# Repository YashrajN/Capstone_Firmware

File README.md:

# Capstone_Firmware
Firmware for autonomous shingle installation robot

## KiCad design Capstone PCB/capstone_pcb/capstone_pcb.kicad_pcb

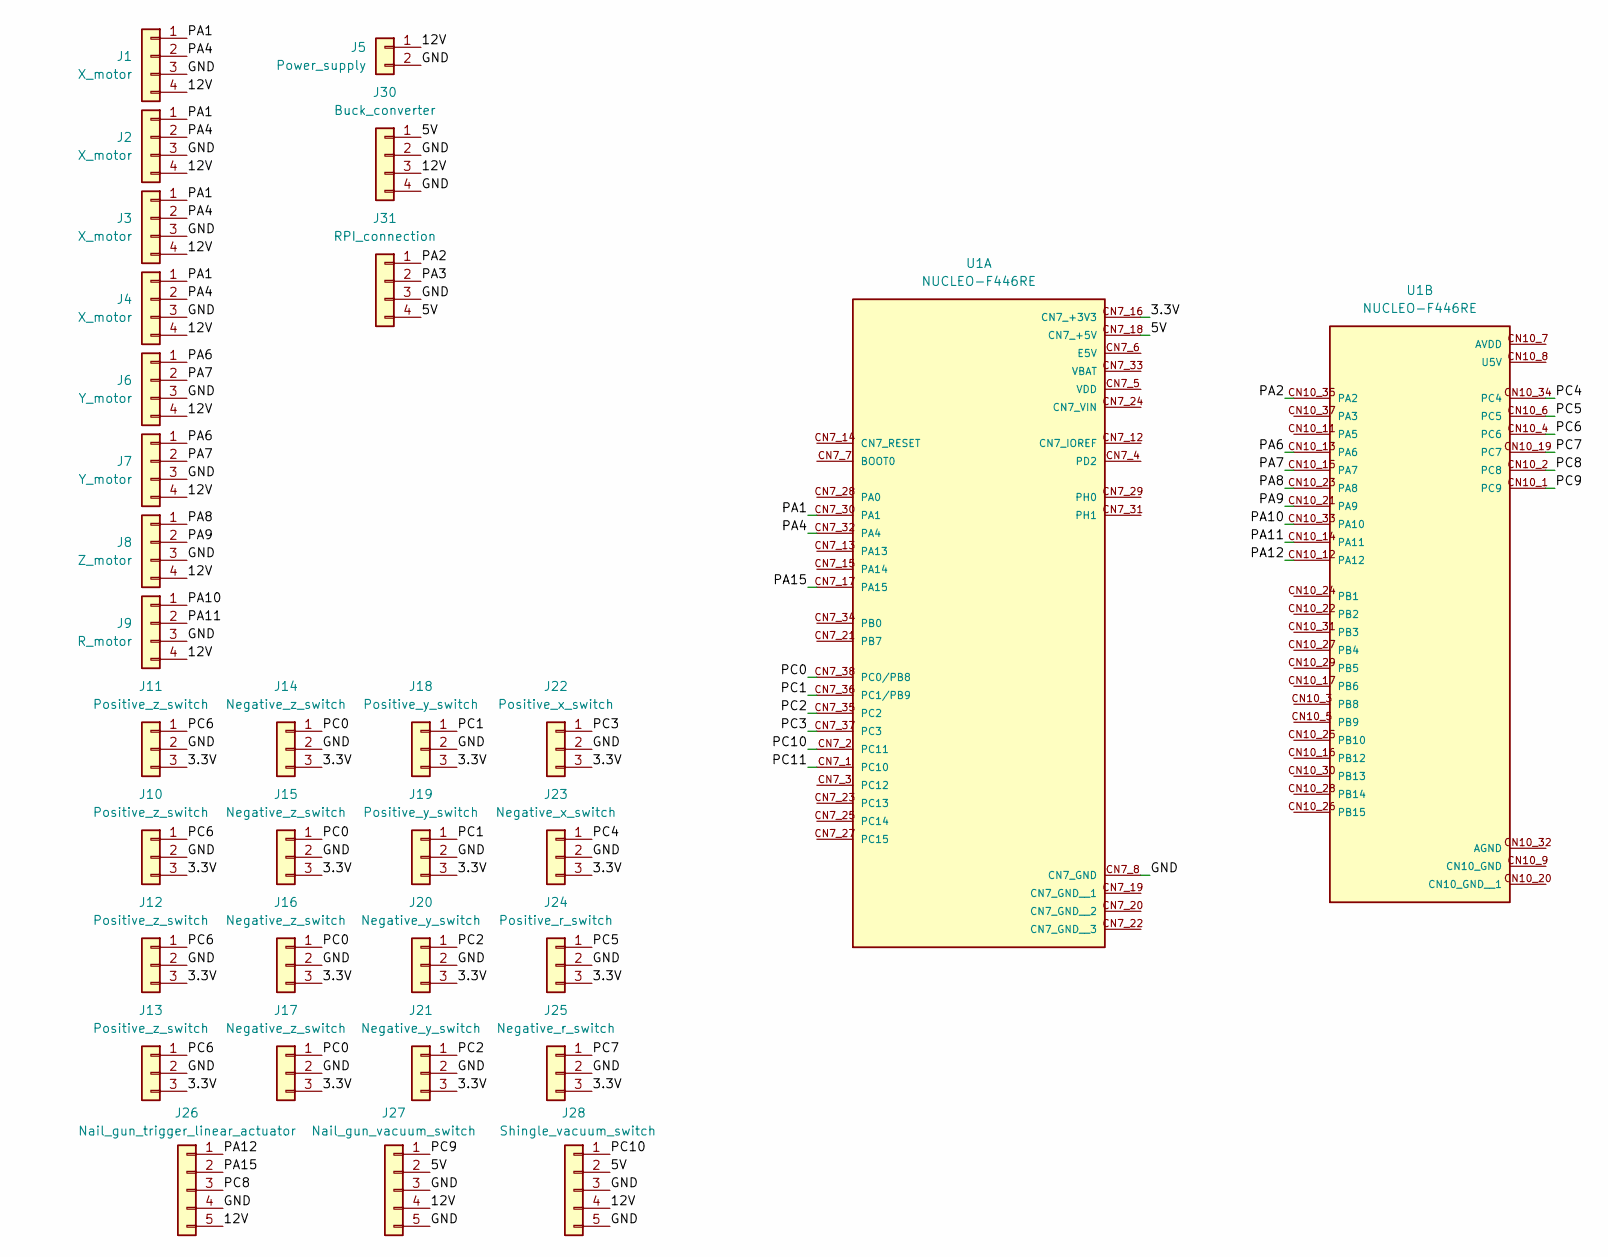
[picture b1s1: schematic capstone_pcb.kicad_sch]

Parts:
J1, J2, J3, J4: X_motor; JST_XH_B4B-XH-A_1x04_P2.50mm_Vertical
J5: Power_supply; JST_VH_B2P-VH_1x02_P3.96mm_Vertical
J6, J7: Y_motor; JST_XH_B4B-XH-A_1x04_P2.50mm_Vertical
J8: Z_motor; JST_XH_B4B-XH-A_1x04_P2.50mm_Vertical
J9: R_motor; JST_XH_B4B-XH-A_1x04_P2.50mm_Vertical
J10, J11, J12, J13: Positive_z_switch; JST_XH_B3B-XH-A_1x03_P2.50mm_Vertical
J14, J15, J16, J17: Negative_z_switch; JST_XH_B3B-XH-A_1x03_P2.50mm_Vertical
J18, J19: Positive_y_switch; JST_XH_B3B-XH-A_1x03_P2.50mm_Vertical
J20, J21: Negative_y_switch; JST_XH_B3B-XH-A_1x03_P2.50mm_Vertical
J22: Positive_x_switch; JST_XH_B3B-XH-A_1x03_P2.50mm_Vertical
J23: Negative_x_switch; JST_XH_B3B-XH-A_1x03_P2.50mm_Vertical
J24: Positive_r_switch; JST_XH_B3B-XH-A_1x03_P2.50mm_Vertical
J25: Negative_r_switch; JST_XH_B3B-XH-A_1x03_P2.50mm_Vertical
J26: Nail_gun_trigger_linear_actuator; JST_XH_B5B-XH-A_1x05_P2.50mm_Vertical
J27: Nail_gun_vacuum_switch; JST_XH_B5B-XH-A_1x05_P2.50mm_Vertical
J28: Shingle_vacuum_switch; JST_XH_B5B-XH-A_1x05_P2.50mm_Vertical
J30: Buck_converter; JST_XH_B4B-XH-A_1x04_P2.50mm_Vertical
J31: RPI_connection; JST_XH_B4B-XH-A_1x04_P2.50mm_Vertical
U1: NUCLEO-F446RE; MODULE_NUCLEO-F446RE; PARTREV 13

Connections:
/3.3V: J10.3, J11.3, J12.3, J13.3, J14.3, J15.3, J16.3, J17.3, J18.3, J19.3, J20.3, J21.3, J22.3, J23.3, J24.3, J25.3, U1.CN7_16 (CN7_+3V3)
/5V: J27.2, J28.2, J30.1, J31.4, U1.CN7_18 (CN7_+5V)
/12V: J1.4, J2.4, J3.4, J4.4, J5.1, J6.4, J7.4, J8.4, J9.4, J26.5, J27.4, J28.4, J30.3
/GND: J1.3, J2.3, J3.3, J4.3, J5.2, J6.3, J7.3, J8.3, J9.3, J10.2, J11.2, J12.2, J13.2, J14.2, J15.2, J16.2, J17.2, J18.2, J19.2, J20.2, J21.2, J22.2, J23.2, J24.2, J25.2, J26.4, J27.3, J27.5, J28.3, J28.5, J30.2, J30.4, J31.3, U1.CN7_8 (CN7_GND)
/PA1: J1.1, J2.1, J3.1, J4.1, U1.CN7_30 (PA1)
/PA2: J31.1, U1.CN10_35 (PA2)
/PA3: J31.2
/PA4: J1.2, J2.2, J3.2, J4.2, U1.CN7_32 (PA4)
/PA6: J6.1, J7.1, U1.CN10_13 (PA6)
/PA7: J6.2, J7.2, U1.CN10_15 (PA7)
/PA8: J8.1, U1.CN10_23 (PA8)
/PA9: J8.2, U1.CN10_21 (PA9)
/PA10: J9.1, U1.CN10_33 (PA10)
/PA11: J9.2, U1.CN10_14 (PA11)
/PA12: J26.1, U1.CN10_12 (PA12)
/PA15: J26.2, U1.CN7_17 (PA15)
/PC0: J14.1, J15.1, J16.1, J17.1, U1.CN7_38 (PC0/PB8)
/PC1: J18.1, J19.1, U1.CN7_36 (PC1/PB9)
/PC2: J20.1, J21.1, U1.CN7_35 (PC2)
/PC3: J22.1, U1.CN7_37 (PC3)
/PC4: J23.1, U1.CN10_34 (PC4)
/PC5: J24.1, U1.CN10_6 (PC5)
/PC6: J10.1, J11.1, J12.1, J13.1, U1.CN10_4 (PC6)
/PC7: J25.1, U1.CN10_19 (PC7)
/PC8: J26.3, U1.CN10_2 (PC8)
/PC9: J27.1, U1.CN10_1 (PC9)
/PC10: J28.1, U1.CN7_2 (PC11)
/PC11: U1.CN7_1 (PC10)

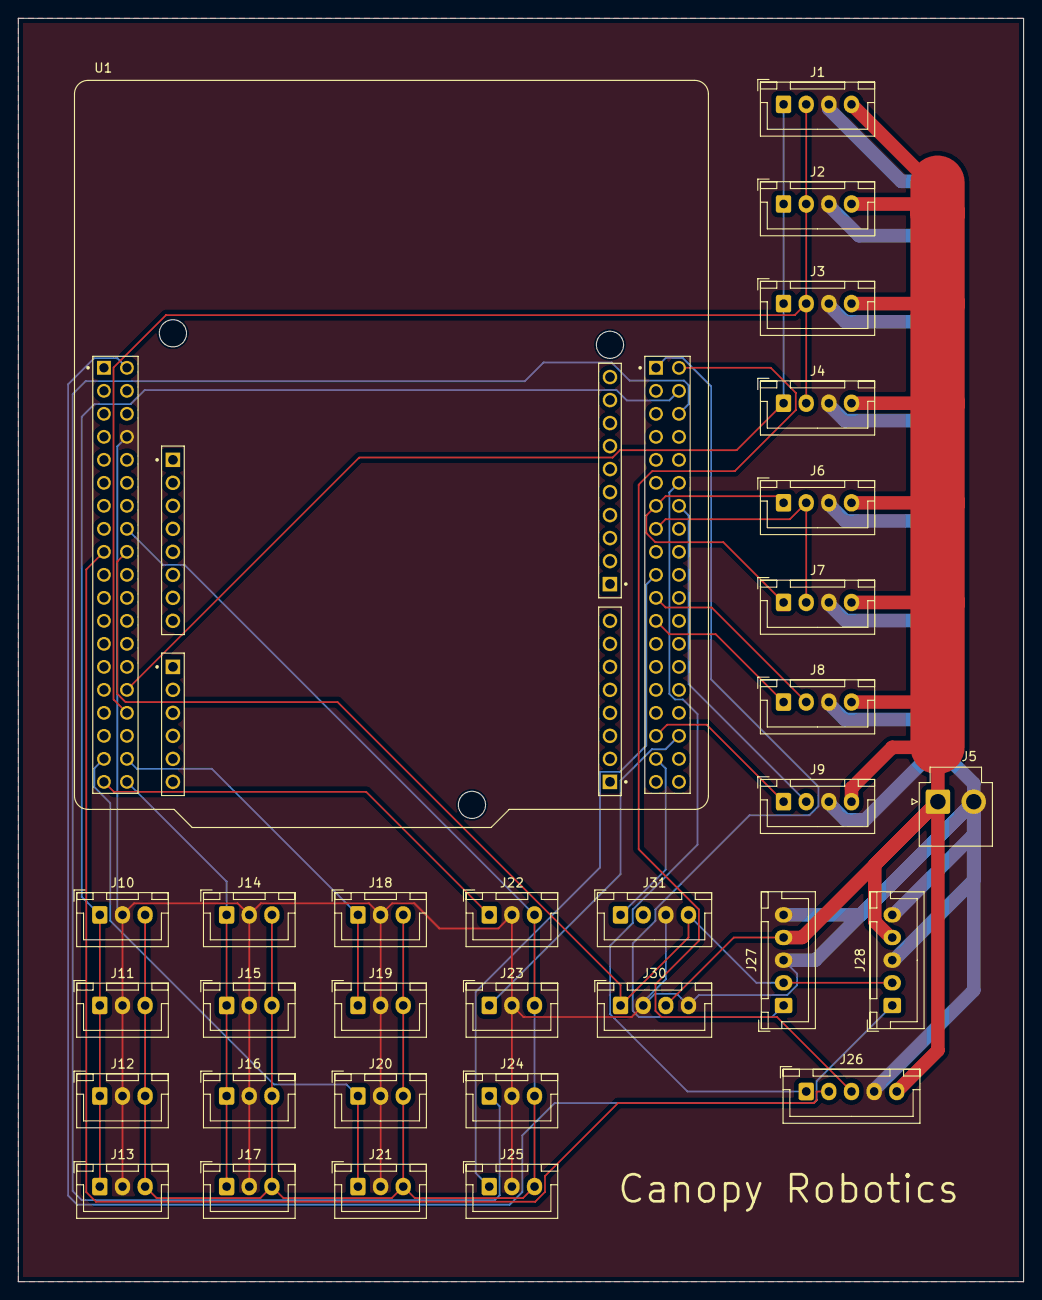
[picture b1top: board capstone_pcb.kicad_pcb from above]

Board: 2 copper layers, 111.0 x 139.5 mm, 31 parts (0 on the bottom side), 26 nets.

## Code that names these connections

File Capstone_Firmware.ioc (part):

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Mcu.Name=STM32F446R(C-E)Tx
Mcu.Package=LQFP64
Mcu.UserName=STM32F446RETx
PA1.Signal=GPIO_Output
PA10.Signal=GPIO_Output
PA11.Signal=GPIO_Output
PA12.Signal=GPIO_Output
PA13.GPIOParameters=GPIO_Label
PA13.GPIO_Label=TMS
PA13.Mode=Serial_Wire
PA13.Signal=SYS_JTMS-SWDIO
PA14.GPIOParameters=GPIO_Label
PA14.GPIO_Label=TCK
PA14.Mode=Serial_Wire
PA14.Signal=SYS_JTCK-SWCLK
PA15.Signal=GPIO_Output
PA2.GPIOParameters=GPIO_Label
PA2.GPIO_Label=USART_TX
PA2.Mode=Asynchronous
PA2.Signal=USART2_TX
PA3.GPIOParameters=GPIO_Label
PA3.GPIO_Label=USART_RX
PA3.Mode=Asynchronous
PA3.Signal=USART2_RX
PA4.Signal=GPIO_Output
PA5.GPIOParameters=GPIO_Label
PA5.GPIO_Label=LD2 [Green Led]
PA5.Signal=GPIO_Output
PA6.Signal=GPIO_Output
PA7.Signal=GPIO_Output
PA8.Signal=GPIO_Output
PA9.Signal=GPIO_Output
PB3.GPIOParameters=GPIO_Label
PB3.GPIO_Label=SWO
PB3.Signal=SYS_JTDO-SWO
PB8.GPIOParameters=GPIO_PuPd,GPIO_ModeDefaultEXTI
PB8.GPIO_ModeDefaultEXTI=GPIO_MODE_IT_RISING_FALLING
PB8.GPIO_PuPd=GPIO_PULLUP
PB8.Signal=GPXTI8
PB9.GPIOParameters=GPIO_PuPd,GPIO_ModeDefaultEXTI
PB9.GPIO_ModeDefaultEXTI=GPIO_MODE_IT_RISING_FALLING
PB9.GPIO_PuPd=GPIO_PULLUP
PB9.Signal=GPXTI9
PC0.GPIOParameters=GPIO_PuPd,GPIO_ModeDefaultEXTI
PC0.GPIO_ModeDefaultEXTI=GPIO_MODE_IT_RISING_FALLING
PC0.GPIO_PuPd=GPIO_PULLUP
PC0.Signal=GPXTI0
PC1.GPIOParameters=GPIO_PuPd,GPIO_ModeDefaultEXTI
PC1.GPIO_ModeDefaultEXTI=GPIO_MODE_IT_RISING_FALLING
PC1.GPIO_PuPd=GPIO_PULLUP
PC1.Signal=GPXTI1
PC10.GPIOParameters=GPIO_PuPd,GPIO_ModeDefaultOutputPP
PC10.GPIO_ModeDefaultOutputPP=GPIO_MODE_OUTPUT_PP
PC10.GPIO_PuPd=GPIO_NOPULL
PC10.Signal=GPIO_Output
PC11.Signal=GPIO_Output
PC13.GPIOParameters=GPIO_Label,GPIO_ModeDefaultEXTI
PC13.GPIO_Label=B1 [Blue PushButton]
PC13.GPIO_ModeDefaultEXTI=GPIO_MODE_IT_FALLING
PC13.Signal=GPXTI13
PC14-OSC32_IN.Mode=LSE-External-Oscillator
PC14-OSC32_IN.Signal=RCC_OSC32_IN
PC15-OSC32_OUT.Mode=LSE-External-Oscillator
PC15-OSC32_OUT.Signal=RCC_OSC32_OUT
PC2.GPIOParameters=GPIO_PuPd,GPIO_ModeDefaultEXTI
PC2.GPIO_ModeDefaultEXTI=GPIO_MODE_IT_RISING_FALLING
PC2.GPIO_PuPd=GPIO_PULLUP
PC2.Signal=GPXTI2
PC3.GPIOParameters=GPIO_PuPd,GPIO_ModeDefaultEXTI
PC3.GPIO_ModeDefaultEXTI=GPIO_MODE_IT_RISING_FALLING
PC3.GPIO_PuPd=GPIO_PULLUP
PC3.Signal=GPXTI3
PC4.GPIOParameters=GPIO_PuPd,GPIO_ModeDefaultEXTI
PC4.GPIO_ModeDefaultEXTI=GPIO_MODE_IT_RISING_FALLING
PC4.GPIO_PuPd=GPIO_PULLUP
PC4.Signal=GPXTI4
PC5.GPIOParameters=GPIO_PuPd,GPIO_ModeDefaultEXTI
PC5.GPIO_ModeDefaultEXTI=GPIO_MODE_IT_RISING_FALLING
PC5.GPIO_PuPd=GPIO_PULLUP
PC5.Signal=GPXTI5
PC6.GPIOParameters=GPIO_PuPd,GPIO_ModeDefaultEXTI
PC6.GPIO_ModeDefaultEXTI=GPIO_MODE_IT_RISING_FALLING
PC6.GPIO_PuPd=GPIO_PULLUP
PC6.Signal=GPXTI6
PC7.GPIOParameters=GPIO_PuPd,GPIO_ModeDefaultEXTI
PC7.GPIO_ModeDefaultEXTI=GPIO_MODE_IT_RISING_FALLING
PC7.GPIO_PuPd=GPIO_PULLUP
PC7.Signal=GPXTI7
PC8.Signal=GPIO_Output
PC9.Signal=GPIO_Output
PH0-OSC_IN.Mode=HSE-External-Oscillator
PH0-OSC_IN.Signal=RCC_OSC_IN
PH1-OSC_OUT.Mode=HSE-External-Oscillator
PH1-OSC_OUT.Signal=RCC_OSC_OUT
RCC.HSE_VALUE=8000000
RCC.SYSCLKFreq_VALUE=84000000
RCC.SYSCLKSource=RCC_SYSCLKSOURCE_PLLCLK
board=NUCLEO-F446RE
boardIOC=true

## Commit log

2025-06-11 capstone firmware
2025-06-11 comms software
